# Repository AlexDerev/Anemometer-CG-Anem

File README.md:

# Портативный анемометр

проект сделан на основе [Official CG-Anem library by ClimateGuard](https://github.com/climateguard/CG-Anem#official-library-for-cg-anem-by-climateguard) и [статьи на Хабре](https://habr.com/ru/post/676348/) 

Цель - попрактиковаться в 3D-моделировании в FreeCAD совместно с дизайном в в KiCAD. И сделать вариант компактного анемометра для параглайдинга.
Исходно набор деталей был взят из статьи:
1. [контроллер WEMOS D1 mini pro](https://aliexpress.ru/item/1005003763905349.html?sku_id=12000027084254255)
2. [USB Модуль зарядки с защитой](https://aliexpress.ru/item/1005003585993852.html?sku_id=12000026386522752)
3. [ADP3338AKC-3.3 регулятор напряжения с низким падением](https://aliexpress.ru/item/4000045988751.html?sku_id=10000000103095880) покупался по линку из статьи. В реальности оказалось подделкой из перепиленного 1117 с падением 1,04 V. В итоге использовался [регулятор MCP1700](https://www.chipdip.ru/product/mcp1700-3302e-to-microchip) в корпусе TO-92.
4. [Экран OLED 1.3"](https://aliexpress.ru/item/1005001621782442.html?sku_id=12000016846377326) вместо 0.96".
5. [Микрик с лапкой на плату](https://roboparts.ru/catalog/kommutatsiya/mikropereklyuchateli_kontsevye_vyklyuchateli/dm3_03p_125v_1a_mikropereklyuchatel/)
6. [Разъем PBS-04 для экрана](https://roboparts.ru/catalog/razemy/shtyrkovye_razyemy/pbs_1x06_razem_na_platu_2_54mm/)
7. [Держатель для 18650 с контактами](https://www.chipdip.ru/product1/8007238837)

## Сравнение с распростаненными у парапланеристов вертушечными анемометрами

### Достоинства
  - Нет вращающихся деталей, нет проблем с подшипниками 
  - Более точный (вероятно). Но нужен прецизионный регулятор напряжения!

### Недостатки

  - Дороже. Типичная вертушка 800 р на Али.
  - Тонкие чувствительные концы. В полевых условиях легко обломать, нужно дополнительно защищать.
  - Отноисительно долгий старт
  - Высокое потребление тока для нагрева горячего конца.
  
  ## Детали реализации
  
  1. Стойки для крепления OLED 11 mm с резьбой M3. Определялось высотой разъема под экран. Впаивать для уменьшения высоты не хотелось.
  2. Диина шурупов для корпуса не менее 20 mm. Исходно сделано под 2.5 mm, но можно рассверлить до 3 mm  в нижней половинке и 2.5 mm в верхней для 3 mm шурупов.
  3. Для кнопки можно использовать пружинку из ручки. Нужно аккуратно рассверлить отверстие в ней до 5 mm.
  4. Для крепления экрана, стоек к плате и сенсора к слайдеру нужны M3 винты с потайной головкой. Длина не более 5 mm.
  5. Исходно печатная плата делалась в Sprint Layout (OLD). В финальном варианте сделана в KiCAD.
  6. 3D модели деталей брались из Интернета, поэтому есть небольшие несостыковки в общей сборке. Дизайн корпуса основывался на реальных деталях. 
  
  ## Планы
  1. Перепроектировать корпус с ипользованием возможности сборки в FreeCAD
  2. Переделать прошивку с выводом графика скорости.
  2. Попробовать уменьшить корпус под использование BL-5C Nokia Li-Ion battery и менее острыми углами.

======================================================================================================
# Handheld Anemometer

Project is based on [Official CG-Anem library by ClimateGuard](https://github.com/climateguard/CG-Anem#official-library-for-cg-anem-by-climateguard) and [habr article](https://habr.com/ru/post/676348/) 

The aim of the project is to practice in 3D-modelling in FreeCAD and electronic design in KiCAD. And to construct the compact anemometer for paraglading.
Initial set of electronic parts was based on the article:
1. [WEMOS D1 mini pro controller](https://aliexpress.ru/item/1005003763905349.html?sku_id=12000027084254255)
2. [USB Li-Ion Charge module](https://aliexpress.ru/item/1005003585993852.html?sku_id=12000026386522752)
3. [ADP3338AKC-3.3 LDO voltage regulator](https://aliexpress.ru/item/4000045988751.html?sku_id=10000000103095880) was taken from the article link. Don't
buy here, it is a fake. Indeed it is remarked 1117 series vith 1,04 V dropout. The [MCP1700 regulator](https://www.chipdip.ru/product/mcp1700-3302e-to-microchip) in TO92 package was used finally.
4. [OLED 1.3" module](https://aliexpress.ru/item/1005001621782442.html?sku_id=12000016846377326) instead of 0.96".
5. [PCB mounted microswitch](https://roboparts.ru/catalog/kommutatsiya/mikropereklyuchateli_kontsevye_vyklyuchateli/dm3_03p_125v_1a_mikropereklyuchatel/)
6. [PBS-04 socket for OLED](https://roboparts.ru/catalog/razemy/shtyrkovye_razyemy/pbs_1x06_razem_na_platu_2_54mm/)
7. [18650 battery holder](https://www.chipdip.ru/product1/8007238837)

## Comparing with conventional rotary handheld anemometers

### Advantages
  - No moving parts - no problems with bearings
  - More accurate (probably). You do need high precision ldo voltage regulator!

### Disadvantages

  - More expensive
  - Sensor ends seem weak and can be broken easily. They need to be additionally protected
  - Relatively long start
  - High current consumption to heat a hotend.
  
  ## Detals
  
  1. OLED screen stands should be 11 mm high and have M3 thread.
  2. The length of case asembling screws should be no less 20 mm. Initially it was supposed to use 2.5 mm screws but you can drill holes up to 3 mm  in bottom part and 2.5 mm in top part to use 3 mm screws.
  3. You can use a spring for button from a pen. In this case you need to drill carefully a hole in the button up to 5 mm diam.
  4. You need to use the short M3 countersunk head screws to attach screen stands to PCB and a sensor plate to a slider. Length should be no more then 5 mm.
  5. PCB layout is designed in Sprint Layout software (OLD). PCB was redesigned in KiCAD.
  6. 3D models of electronic parts were taken from Internet and they seem slightly differ from real parts. The case design is based on the real ones. 
  
  ## TO-DO List
  1. Redesign the case in FreeCAD to use the assembling features
  2. Try to make a new compact case for BL-5C Nokia Li-Ion battery and without sharp corners.

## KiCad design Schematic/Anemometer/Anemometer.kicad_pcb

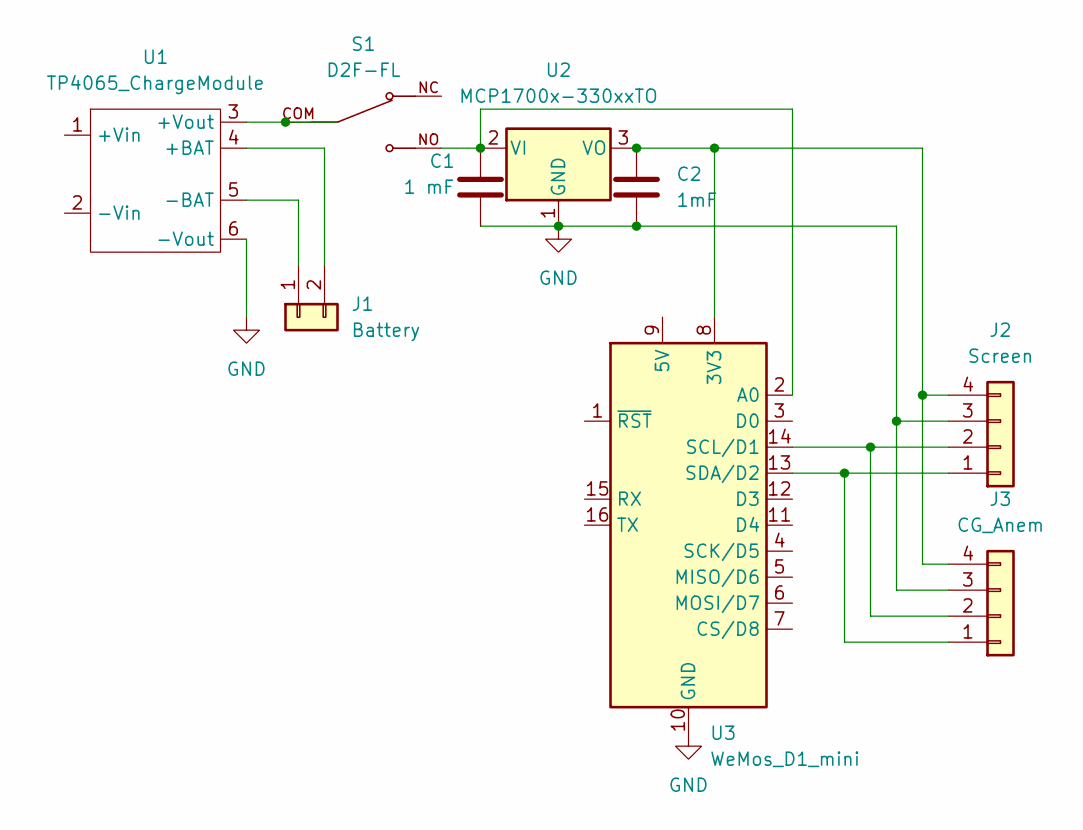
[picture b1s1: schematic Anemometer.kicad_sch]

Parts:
C1: 1 mF; C_1206_3216Metric
C2: 1mF; C_1206_3216Metric
J1: Battery; JST_EH_S2B-EH_1x02_P2.50mm_Horizontal
J2: Screen; PinSocket_1x04_P2.54mm_Vertical
J3: CG_Anem; JST_EH_S4B-EH_1x04_P2.50mm_Horizontal
S1: D2F-FL; SW_D2F-FL; PARTREV N/A
U1: TP4065_ChargeModule
U2: MCP1700x-330xxTO; TO-92_Inline
U3: WeMos_D1_mini; WEMOS_D1_mini_light

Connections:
GND: C1.2, C2.2, J2.3, J3.3, U1.6 (-Vout), U2.1 (GND), U3.10 (GND)
unnamed: C1.1, S1.NO, U2.2 (VI), U3.2 (A0)
unnamed: C2.1, J2.4, J3.4, U2.3 (VO), U3.8 (3V3)
unnamed: J2.1, J3.1, U3.13 (SDA/D2)
unnamed: J2.2, J3.2, U3.14 (SCL/D1)
unnamed: S1.COM, U1.3 (+Vout)
unnamed: J1.2, U1.4 (+BAT)
unnamed: J1.1, U1.5 (-BAT)

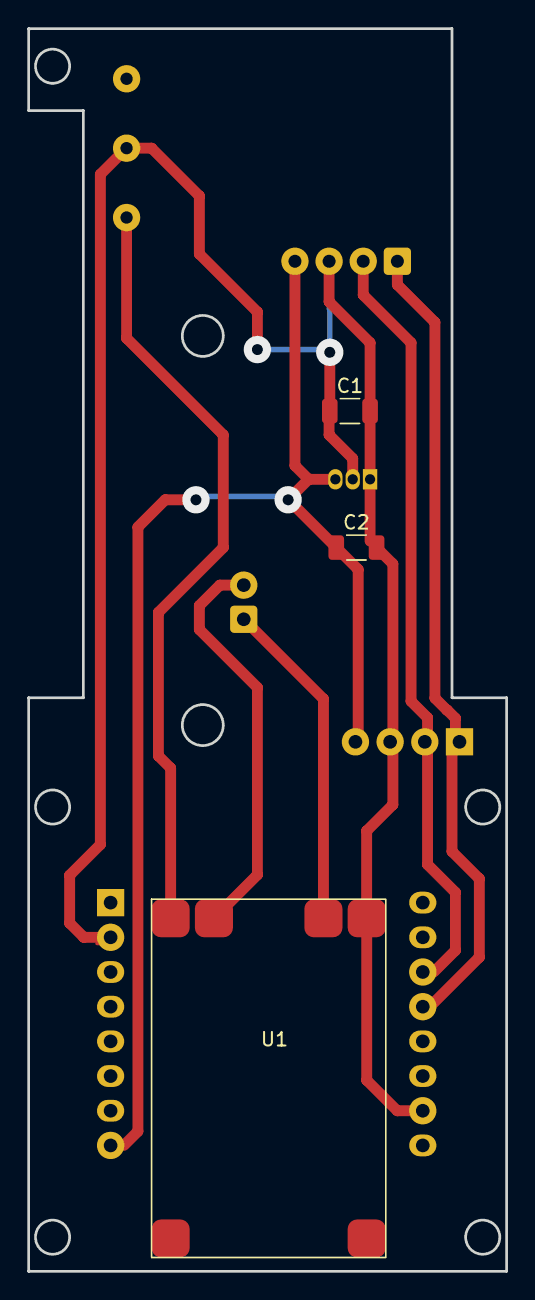
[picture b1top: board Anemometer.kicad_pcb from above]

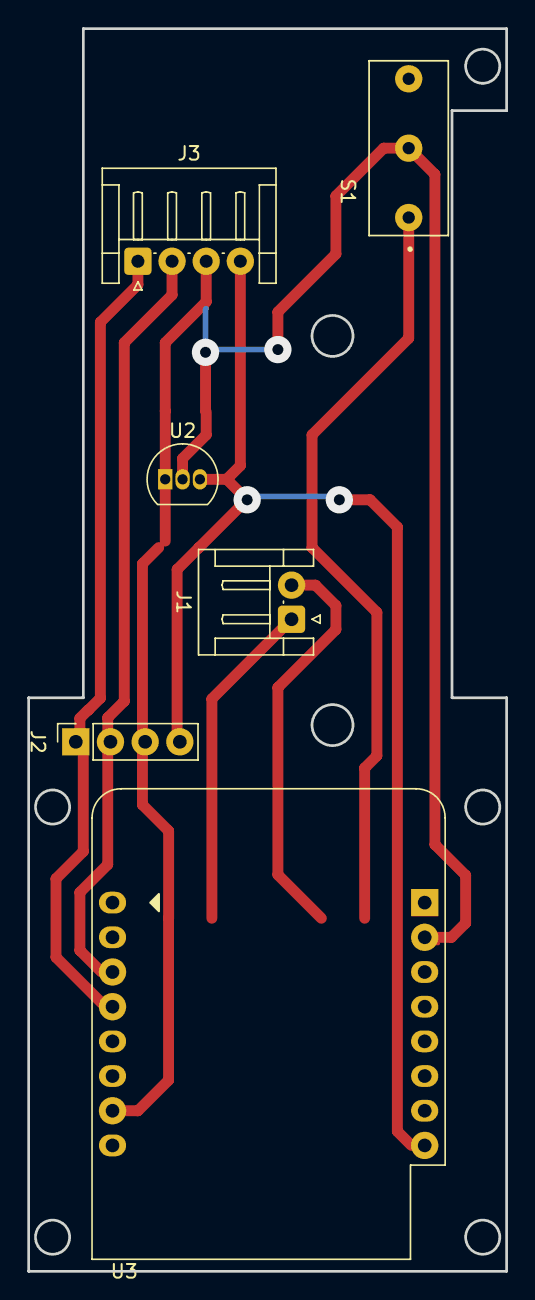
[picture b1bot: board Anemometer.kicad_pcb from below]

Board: 2 copper layers, 35.0 x 91.0 mm, 9 parts (6 on the bottom side), 8 nets.

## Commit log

2022-12-26 3D Case model added
2022-12-27 Fix cover slot on case top part
2022-12-27 Top cover and slider fixed
2022-12-30 PCB Created
    Designed in Sprint Layout
2022-12-30 Fix errors after test assembling
    Не были учтены торчащие выводы из материнки. Не было места для головок винтов крепления сенсора к слайдеру. Слайдер и сенсор опущены на 1.5 мм. Отверстия крепления в слайдере уменьшены для нарезки ре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
2023-01-01 Залит скетч из примера
2023-01-01 Fixes after full assembling
    Отверстия в слайдере увеличены обратно, сделаны под потайную головку. На PCB аналогично увеличены отверстия под стойки для потайных М3. Увеличены размеры отверстий под USB, коннектор не входил до кон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
2023-01-03 PCB Update
    Убрано соединение SLEEP сенсора на землю.
    Добавлена PCB для регулятора LD39050. Есть в продаже по разумной цене. Но монтировать тяжелее.
2023-01-05 Create Main PCB(MCP1700 reg).lay6
    Сделана разводка под регулятор MCP1770 в корпусе TO-92. У него ток всего 250mA, немного хуже точность регулирования, но значительно дешевле.
2023-01-05 Update Main PCB.lay6
    Небольшая ошибка в разводке земли. Некритично, но все-таки
2023-01-06 Schematic and PCB in KiCAD
    Схема и плата для регулятора MCP1700 в корпусе ТО-92
2023-01-08 Case and PCB Fixes
    Правки сборки после перевода на стаб MCP1700.
    Вместо полных вырезов для USB сделаны выемки. Их достаточно.
    Передвинут разъем к сенсору на PCB, иначе провода загибаются прям впритирку к корпусу.
2023-01-08 Create cg_amen_1v1.step
    Добавлен 3D модель сенсора
2023-01-08 Code for sensor testing
2023-01-11 Added PCB 3D model
2023-01-12 Detaled 3D models added
    Добавлены нормальные 3D модели базовой платы, экрана, стойки и винты крепления.
2023-01-22 light modifications
    +Hardware ver
    -Vol. consumption
2023-01-23 PCB Updated
    Перемычка мешала слайдеру
2023-01-24 Sprint lauout PCB directory renamed
2023-01-24 Update main.cpp
    Начата переделка прошивки. Обновлен стартовый экран добавлен прогресс ожидания, убраны лишние данные с рабочего экрана.
2023-01-31 Flow Plot added (Draft)
    Добавлен класс для расчета точек графика скорости, чтобы можно было выводить на экран
2023-02-01 Update Anemometer case.FCStd
    Слегка поправлено окошко для экрана, немного заходило на нижнюю часть
2023-02-01 Comments added
    Расширены комментарии
2023-02-09 Rearranged main screen
    Облагорожен основной экран, выведены верхние и нижние границы, переставлены значения и пр.
2023-02-10 Fine tuning
2023-02-11 Updated display window position modified: Case/Anemometer case.FCStd
